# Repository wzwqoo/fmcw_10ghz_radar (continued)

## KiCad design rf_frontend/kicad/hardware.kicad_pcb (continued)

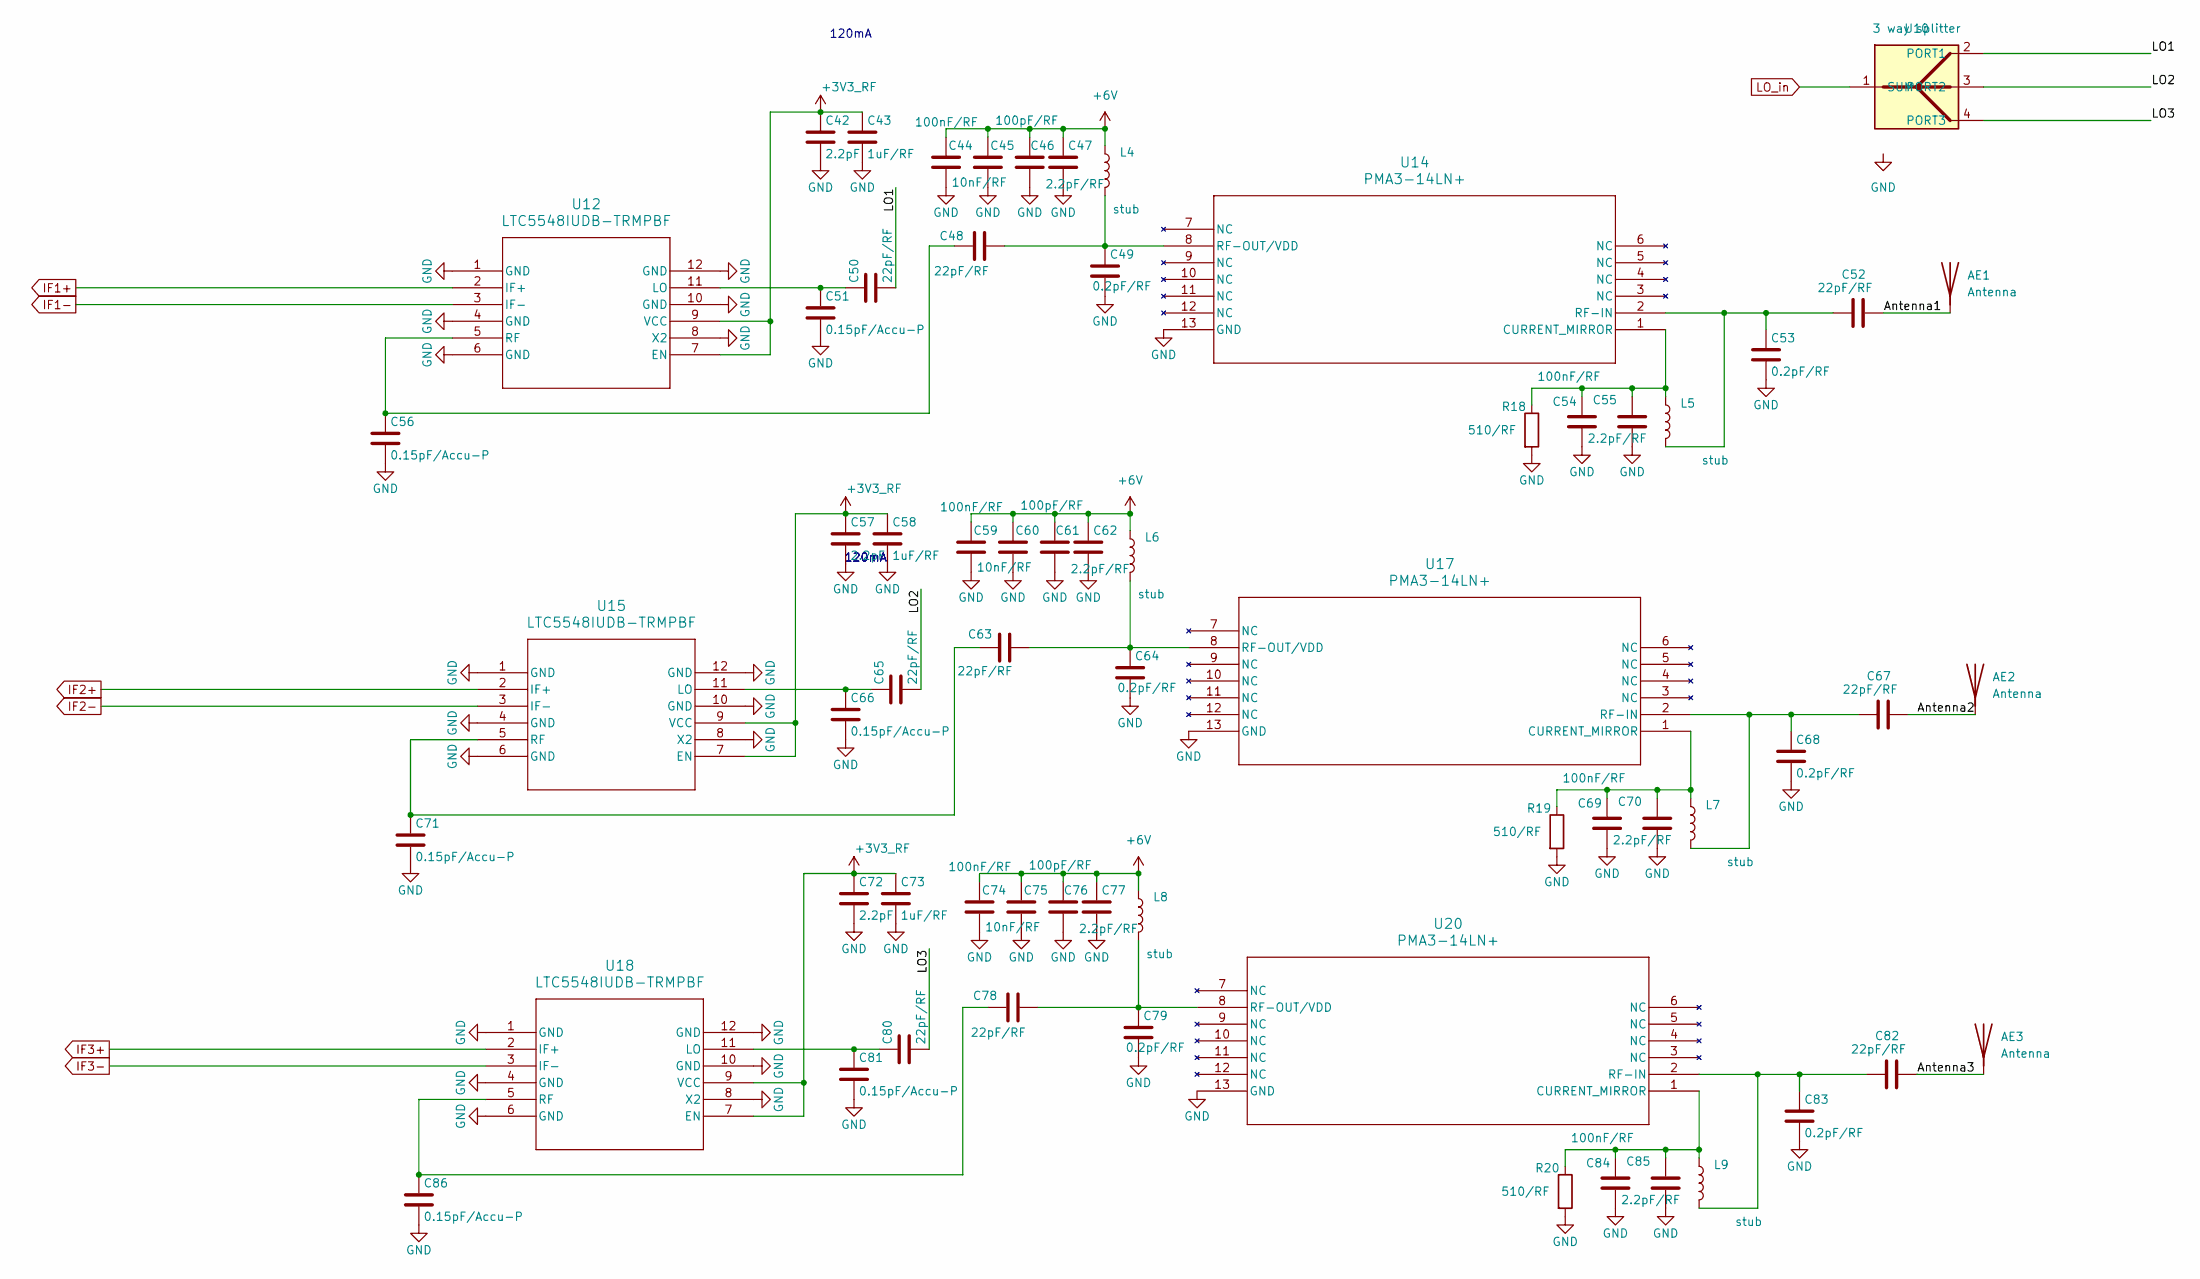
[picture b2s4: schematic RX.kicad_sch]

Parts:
AE1, AE2, AE3: Antenna; antenna
C42, C57, C72: 2.2pF; C_0201_0603Metric
C43, C58, C73: 1uF/RF; C_0402_1005Metric
C44, C54, C59, C69, C74, C84: 100nF/RF; C_0402_1005Metric
C45, C60, C75: 10nF/RF; C_0402_1005Metric
C46, C61, C76: 100pF/RF; C_0402_1005Metric
C47, C55, C62, C70, C77, C85: 2.2pF/RF; C_0402_1005Metric
C48, C50, C52, C63, C65, C67, C78, C80, C82: 22pF/RF; C_0201_0603Metric
C49, C53, C64, C68, C79, C83: 0.2pF/RF; C_0201_0603Metric
C51, C56, C66, C71, C81, C86: 0.15pF/Accu-P; C_0201_0603Metric
L4, L5, L6, L7, L8, L9: stub; NetTie-2_SMD_Pad0.5mm
R18, R19, R20: 510/RF; R_0402_1005Metric
U10: 3 way splitter; splitter
U12, U15, U18: LTC5548IUDB-TRMPBF; QFN-12-1EP_3x3mm_P0.5mm_EP1.45x1.45mm
U14, U17, U20: PMA3-14LN+; VQFN-12-1EP_4x4mm_P0.8mm_EP2.1x2.1mm; Part# PMA3-14LN+

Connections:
+3V3_RF: C42.1, C43.1, C57.1, C58.1, C72.1, C73.1, U12.7 (EN), U12.9 (VCC), U15.7 (EN), U15.9 (VCC), U18.7 (EN), U18.9 (VCC); also elsewhere on the board
+6V: C44.1, C45.1, C46.1, C47.1, C59.1, C60.1, C61.1, C62.1, C74.1, C75.1, C76.1, C77.1, L4.1, L6.1, L8.1; also elsewhere on the board
/RX/Antenna1: AE1.1 (A_1), C52.2
/RX/Antenna2: AE2.1 (A_1), C67.2
/RX/Antenna3: AE3.1 (A_1), C82.2
/RX/LO1: C50.2, U10.2 (PORT1)
/RX/LO2: C65.2, U10.3 (PORT2)
/RX/LO3: C80.2, U10.4 (PORT3)
GND: C42.2, C43.2, C44.2, C45.2, C46.2, C47.2, C49.2, C51.2, C53.2, C54.2, C55.2, C56.2, C57.2, C58.2, C59.2, C60.2, C61.2, C62.2, C64.2, C66.2, C68.2, C69.2, C70.2, C71.2, C72.2, C73.2, C74.2, C75.2, C76.2, C77.2, C79.2, C81.2, C83.2, C84.2, C85.2, C86.2, R18.2, R19.2, R20.2, U12.1 (GND), U12.4 (GND), U12.6 (GND), U12.8 (X2), U12.10 (GND), U12.12 (GND), U12.13, U14.13 (GND), U15.1 (GND), U15.4 (GND), U15.6 (GND), U15.8 (X2), U15.10 (GND), U15.12 (GND), U15.13, U17.13 (GND), U18.1 (GND), U18.4 (GND), U18.6 (GND), U18.8 (X2), U18.10 (GND), U18.12 (GND), U18.13, U20.13 (GND); also elsewhere on the board
IF1+: U12.2 (IF+); also elsewhere on the board
IF1-: U12.3 (IF-); also elsewhere on the board
IF2+: U15.2 (IF+); also elsewhere on the board
IF2-: U15.3 (IF-); also elsewhere on the board
IF3+: U18.2 (IF+); also elsewhere on the board
IF3-: U18.3 (IF-); also elsewhere on the board
LO_in: U10.1 (SUM); also elsewhere on the board
unnamed: C50.1, C51.1, U12.11 (LO)
unnamed: C48.1, C56.1, U12.5 (RF)
unnamed: C54.1, C55.1, L5.1, R18.1, U14.1 (CURRENT_MIRROR)
unnamed: C52.1, C53.1, L5.2, U14.2 (RF-IN)
unnamed: C48.2, C49.1, L4.2, U14.8 (RF-OUT/VDD)
unnamed: C65.1, C66.1, U15.11 (LO)
unnamed: C63.1, C71.1, U15.5 (RF)
unnamed: C69.1, C70.1, L7.1, R19.1, U17.1 (CURRENT_MIRROR)
unnamed: C67.1, C68.1, L7.2, U17.2 (RF-IN)
unnamed: C63.2, C64.1, L6.2, U17.8 (RF-OUT/VDD)
unnamed: C80.1, C81.1, U18.11 (LO)
unnamed: C78.1, C86.1, U18.5 (RF)
unnamed: C84.1, C85.1, L9.1, R20.1, U20.1 (CURRENT_MIRROR)
unnamed: C82.1, C83.1, L9.2, U20.2 (RF-IN)
unnamed: C78.2, C79.1, L8.2, U20.8 (RF-OUT/VDD)

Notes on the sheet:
120mA

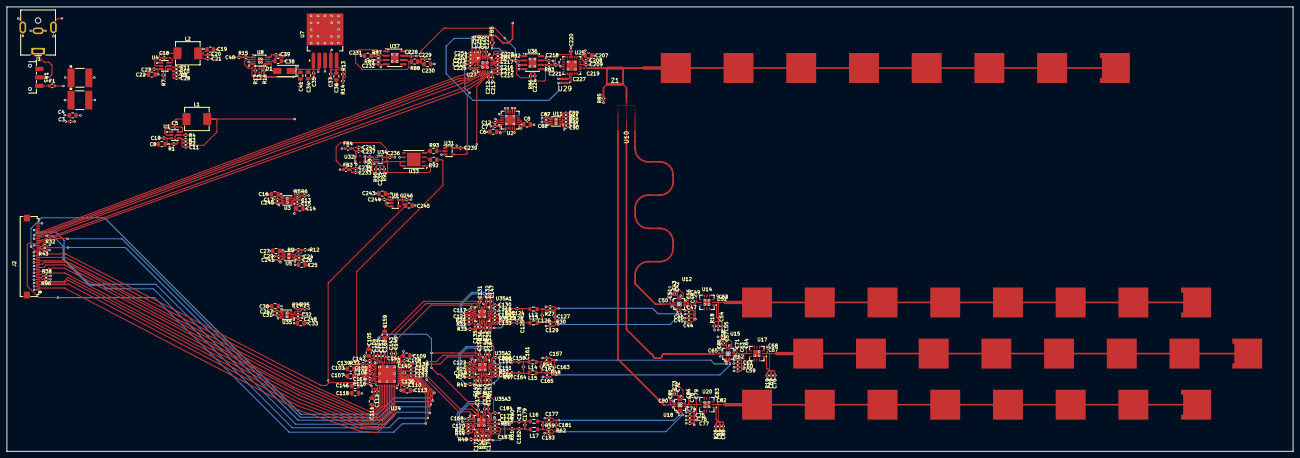
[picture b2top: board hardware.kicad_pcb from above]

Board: 4 copper layers, 377.3 x 130.4 mm, 351 parts (0 on the bottom side), 188 nets.

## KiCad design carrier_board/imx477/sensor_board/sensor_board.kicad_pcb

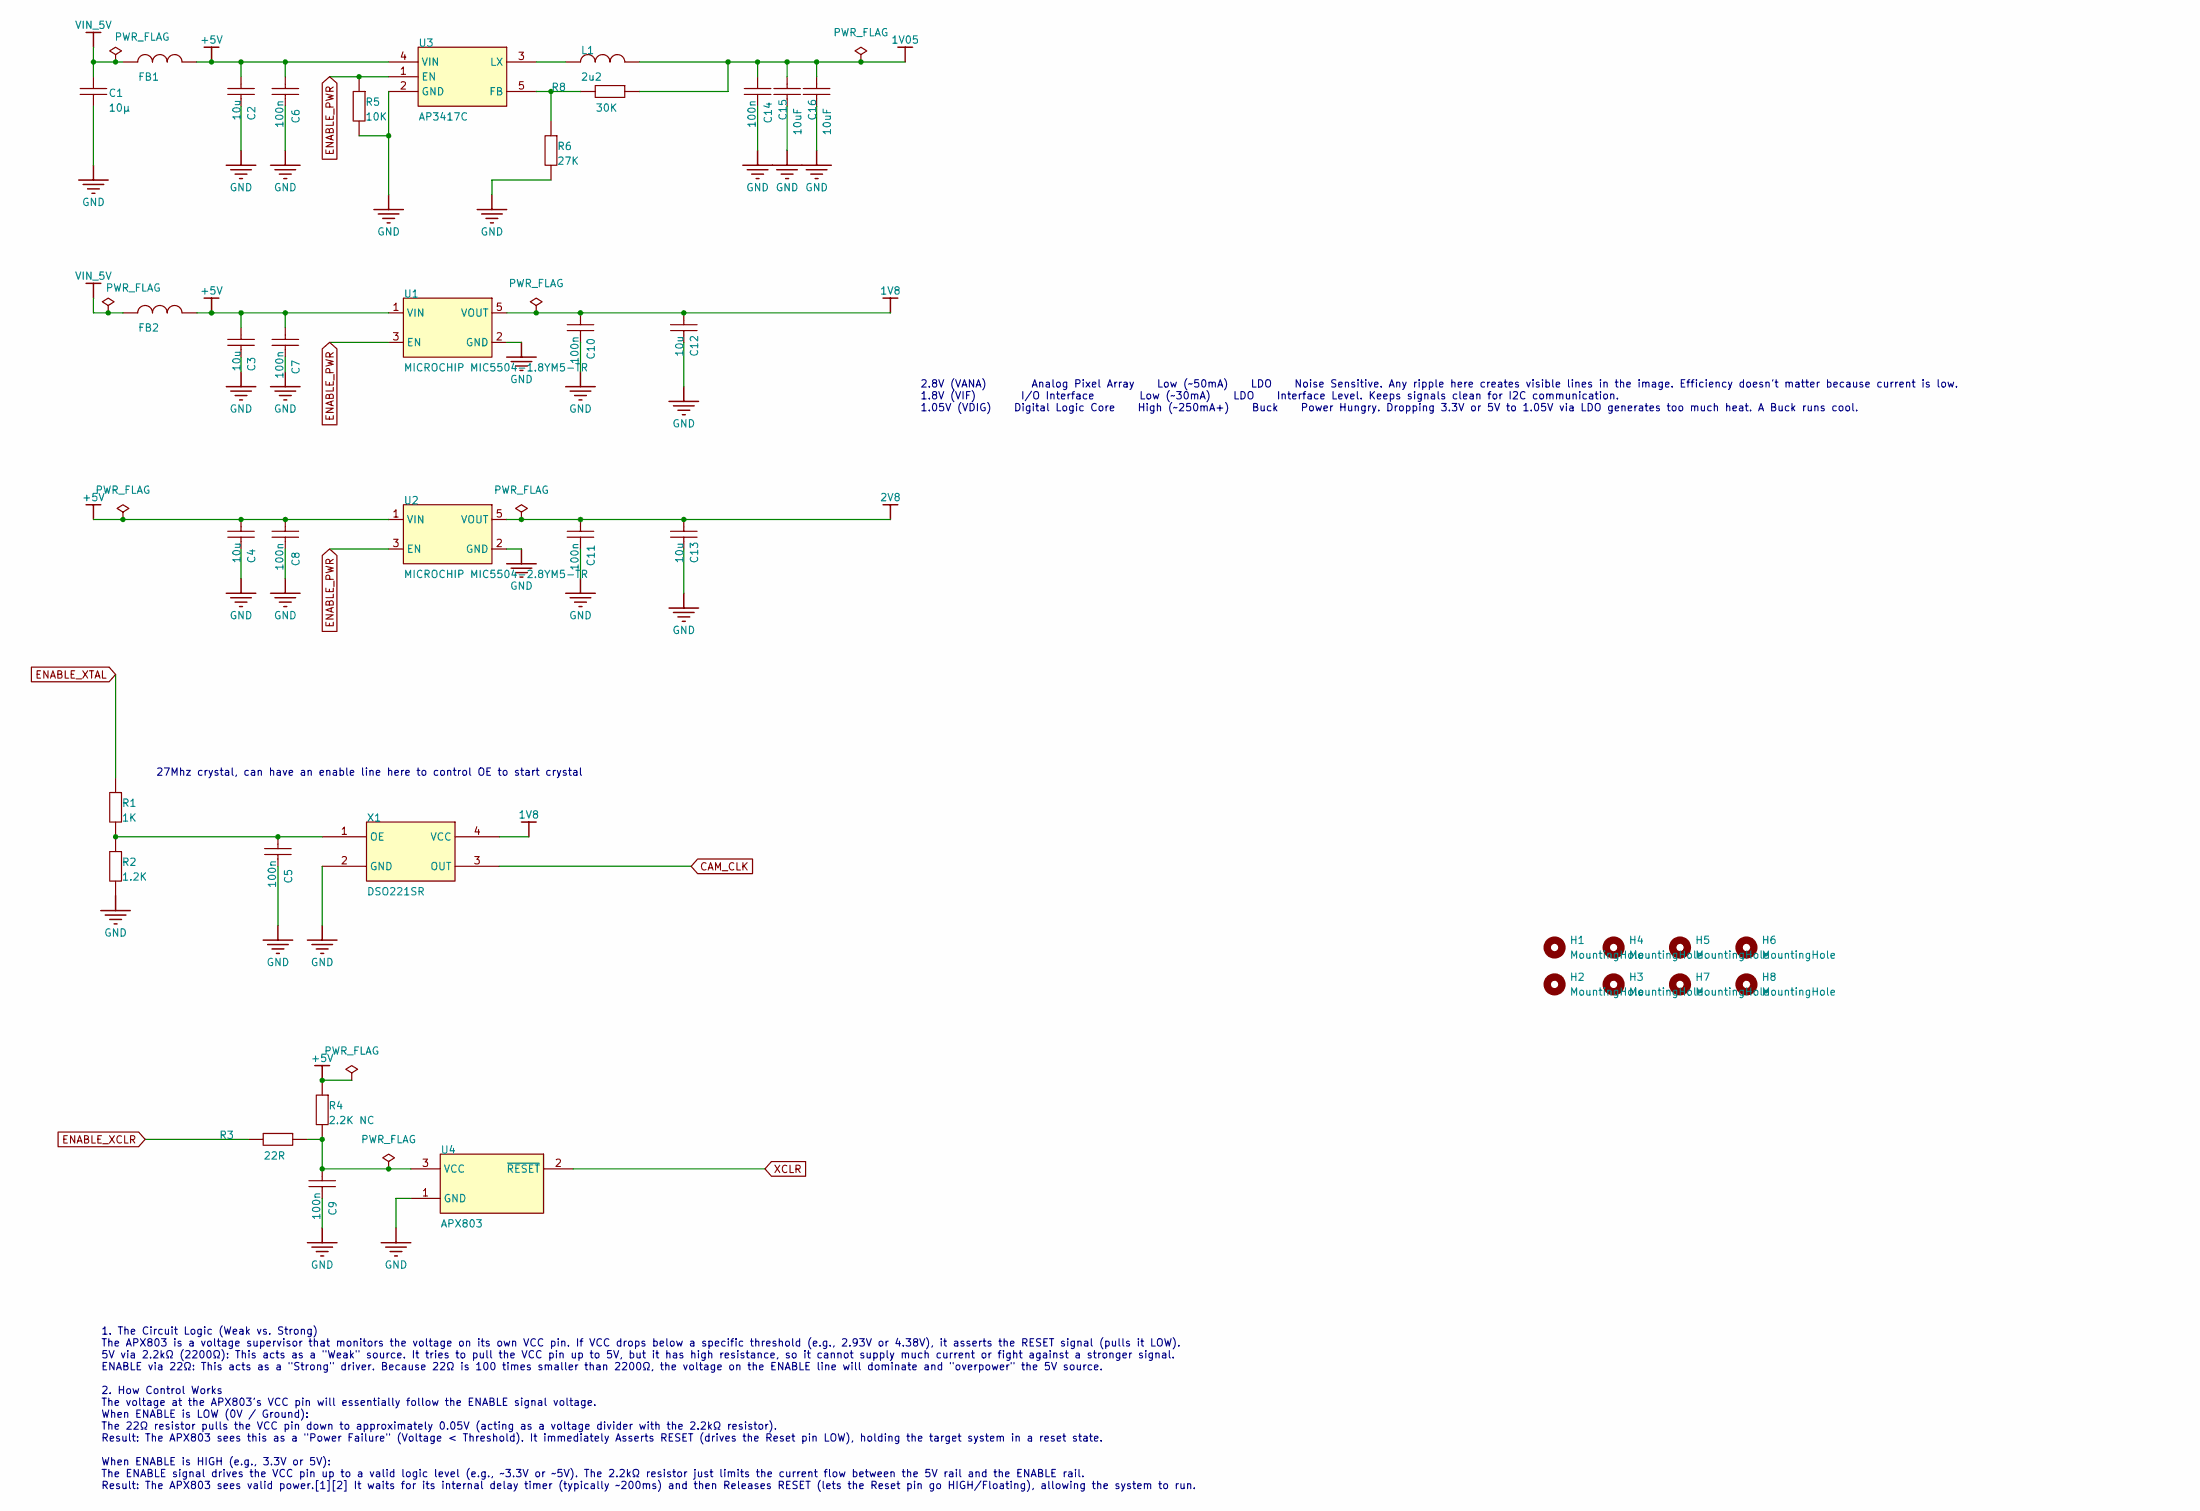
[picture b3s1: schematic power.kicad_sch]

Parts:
C1: 10uF; C_0805_2012Metric; TOLERANCE ±20%; RATINGS 50V; X5R; MANUFACTURER PART NUMBE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 UMK325BJ106MM-T; LCSC Part # C88484
C2, C3, C4, C12, C13: 10uF; C_0805_2012Metric; RATINGS 50V; NP0; VOLTAGE - RATED 50V; MANUFACTURER PART NUMBE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 06035A561JAT2A; LCSC Part # C88484
C5, C6, C7, C8, C9, C10, C11, C14: 100nF; C_0805_2012Metric; TOLERANCE ±10%; RATINGS 16V; X7R; MANUFACTURER PART NUMBE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 CC0402KRX7R7BB103; LCSC Part # C49678
C15, C16: 10uF; C_0805_2012Metric; TOLERANCE ±10%; RATINGS 16V; X5R; MANUFACTURER PART NUMBE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 EMK212BJ475KG-T; LCSC Part # C88484
FB1, FB2: 1 kΩ @ 100 MHz; L_0805_2012Metric; Part# MPZ2012S102AT000; LCSC Part # C76817
H1, H2, H3, H4, H5, H6, H7, H8: MountingHole; MountingHole_2.5mm
L1: 2u2; L_Taiyo-Yuden_MD-4040; Part# CMLO0420H2R2MTT; LCSC Part # C438930
R1: 1K; R_0805_2012Metric; RATINGS 1/16 W; TOLERANCE ±5%; MANUFACTURER PART NUMBE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 RC0402JR-073K3L; LCSC Part # C95781
R2: 1.2K; R_0805_2012Metric; RATINGS 1/16 W; TOLERANCE ±5%; MANUFACTURER PART NUMBE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 RC0402JR-073K3L; LCSC Part # C114526
R3: 22; R_0805_2012Metric; RATINGS 1/16 W; TOLERANCE ±5%; MANUFACTURER PART NUMBE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 RC0402JR-073K3L; LCSC Part # C107702
R4: 2.2K; R_0805_2012Metric; RATINGS 1/16 W; TOLERANCE ±5%; MANUFACTURER PART NUMBE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 RC0402JR-073K3L; LCSC Part # C114237
R5: 10K; R_0805_2012Metric; RATINGS 1/16 W; TOLERANCE ±5%; MANUFACTURER PART NUMBE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 RC0402JR-073K3L; LCSC Part # C100047
R6: 27K; R_0805_2012Metric; RATINGS 1/16 W; TOLERANCE ±5%; MANUFACTURER PART NUMBE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 RC0402JR-073K3L; LCSC Part # C728647
R8: 30K; R_0805_2012Metric; RATINGS 1/16 W; TOLERANCE ±5%; MANUFACTURER PART NUMBE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 RC0402JR-073K3L; LCSC Part # C126352
U1: MICROCHIP MIC5504-1.8YM5-TR; SOT-23-5; Part# MIC5504-1.8YM5-TR; LCSC Part # C626116
U2: MICROCHIP MIC5504-2.8YM5-TR; SOT-23-5; Part# MIC5504-2.8YM5-TR; LCSC Part # C95749
U3: AP3417C; SOT-23-5; Part# AP3417CKTR-G1; LCSC Part # C500759
U4: APX803; SOT-23-3; Part# APX803S-23SA-7; LCSC Part # C2067713
X1: DSO221SR; Crystal_SMD_2520-4Pin_2.5x2.0mm

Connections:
1V05: C14.2, C15.1, C16.1, L1.2, R8.2; also elsewhere on the board
1V8: C10.2, C12.1, U1.5 (VOUT), X1.4 (VCC); also elsewhere on the board
2V8: C11.2, C13.1, U2.5 (VOUT); also elsewhere on the board
+5V: C2.1, C3.1, C4.1, C6.2, C7.2, C8.2, FB1.2, FB2.2, R4.2, U1.1 (VIN), U2.1 (VIN), U3.4 (VIN)
CAM_CLK: X1.3 (OUT); also elsewhere on the board
ENABLE_PWR: R5.2, U1.3 (EN), U2.3 (EN), U3.1 (EN); also elsewhere on the board
ENABLE_XCLR: R3.1; also elsewhere on the board
ENABLE_XTAL: R1.2; also elsewhere on the board
GND: C1.2, C2.2, C3.2, C4.2, C5.1, C6.1, C7.1, C8.1, C9.1, C10.1, C11.1, C12.2, C13.2, C14.1, C15.2, C16.2, R2.1, R5.1, R6.1, U1.2 (GND), U2.2 (GND), U3.2 (GND), U4.1 (GND), X1.2 (GND); also elsewhere on the board
unnamed: R6.2, R8.1, U3.5 (FB)
unnamed: L1.1, U3.3 (LX)
unnamed: C9.2, R3.2, R4.1, U4.3 (VCC)
unnamed: C5.2, R1.1, R2.2, X1.1 (OE)
VIN_5V: C1.1, FB1.1, FB2.1; also elsewhere on the board
XCLR: U4.2 (~RESET); also elsewhere on the board

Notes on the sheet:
1. The Circuit Logic (Weak vs. Strong) The APX803 is a voltage supervisor that monitors the voltage on its own VCC pin. If VCC drops below a specific threshold (e.g., 2.93V or 4.38V), it asserts the RESET signal (pulls it LOW). 5V via 2.2kΩ (2200Ω): This acts as a "Weak" source. It tries to pull th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
2.8V (VANA) Analog Pixel Array Low (~50mA) LDO Noise Sensitive. Any ripple here creates visible lines in the image. Efficiency doesn't matter because current is low. 1.8V (VIF) I/O Interface Low (~30mA) LDO Interface Level. Keeps signals clean for I2C communication. 1.05V (VDIG) Digital Logic Core 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
27Mhz crystal, can have an enable line here to control OE to start crystal

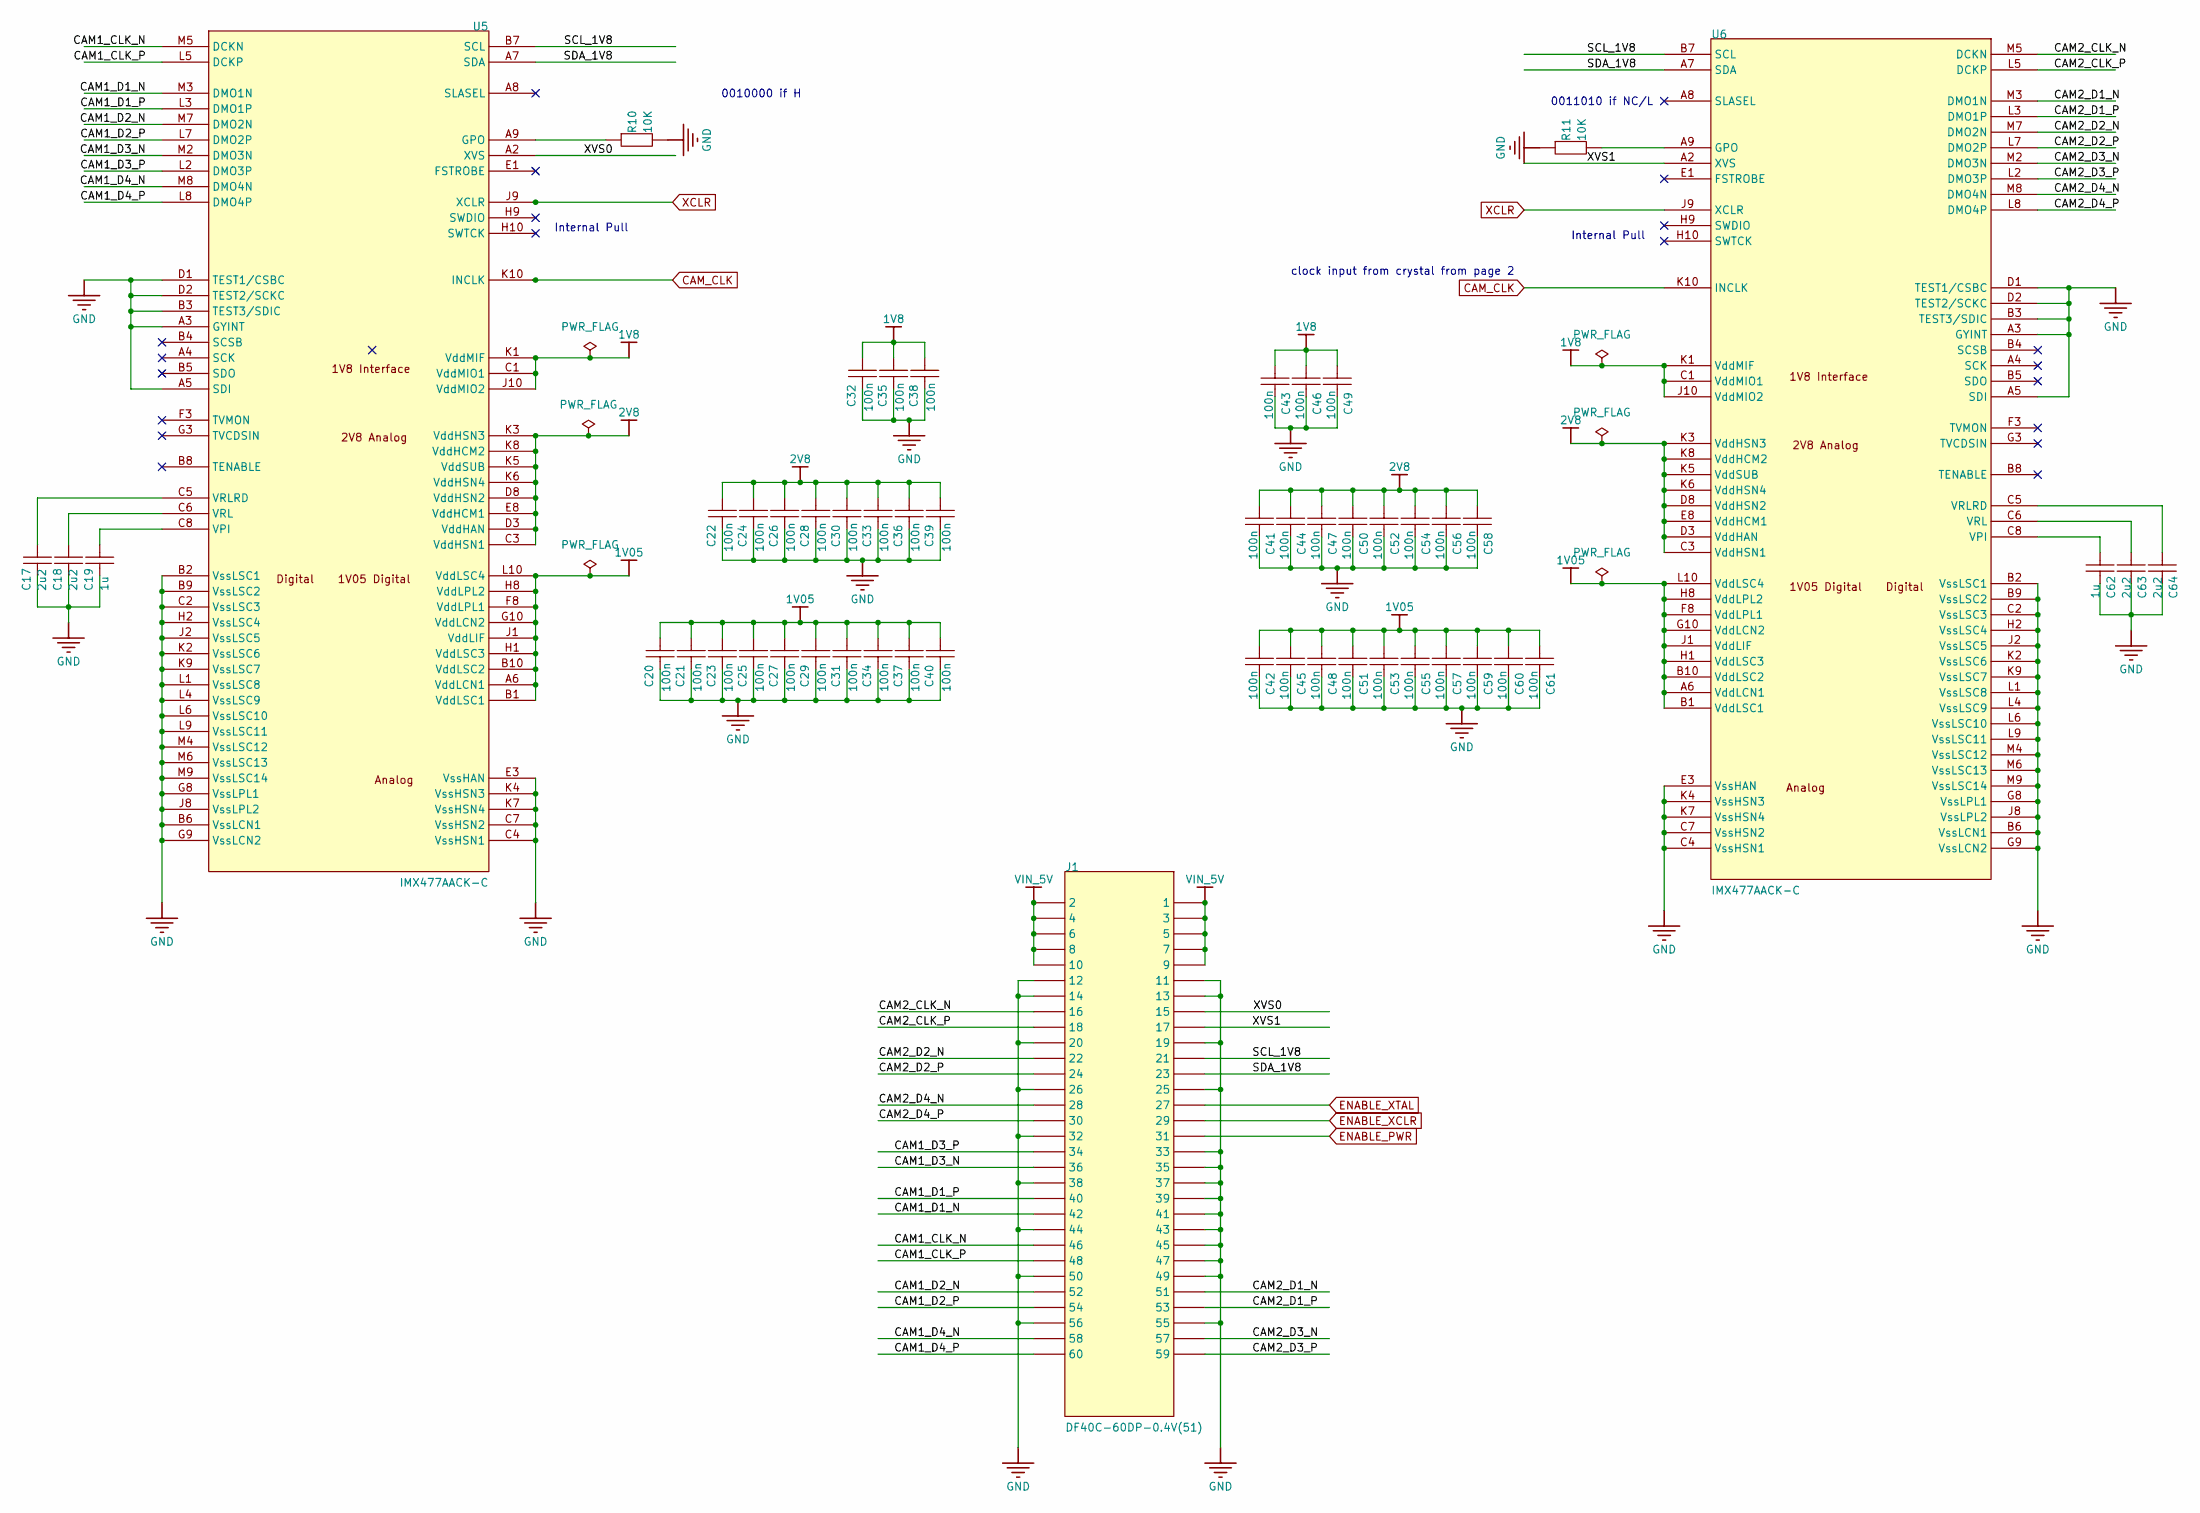
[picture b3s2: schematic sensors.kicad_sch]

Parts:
C17, C18, C19, C62, C63, C64: 10uF; C_0805_2012Metric; RATINGS 50V; NP0; VOLTAGE - RATED 50V; MANUFACTURER PART NUMBE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 06035A561JAT2A; LCSC Part # C88484
C20, C21, C22, C23, C24, C25, C26, C27, C28, C29, C30, C31, C32, C33, C34, C35, C36, C37, C38, C39, C40, C41, C42, C43, C44, C45, C46, C47, C48, C49, C50, C51, C52, C53, C54, C55, C56, C57, C58, C59, C60, C61: 100nF; C_0805_2012Metric; TOLERANCE ±10%; RATINGS 16V; X7R; MANUFACTURER PART NUMBE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 CC0402KRX7R7BB103; LCSC Part # C49678
J1: DF40C-60DP-0.4V(51); Hirose_DF40C-60DP-0.4V_2x30-1MP_P0.4mm; Part# DF40C-60DP-0.4V(51); LCSC Part # C424647
R10, R11: 10K; R_0805_2012Metric; RATINGS 1/16 W; TOLERANCE ±5%; MANUFACTURER PART NUMBE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 RC0402JR-073K3L; LCSC Part # C100047
U5, U6: IMX477AACK-C; LGA-92_L10.5-W8.5-P0.80_IMX477-AAPK-C

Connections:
1V05: C20.2, C21.2, C23.2, C25.2, C27.2, C29.2, C31.2, C34.2, C37.2, C40.2, C42.2, C45.2, C48.2, C51.2, C53.2, C55.2, C57.2, C59.2, C60.2, C61.2, U5.A6 (VddLCN1), U5.B1 (VddLSC1), U5.B10 (VddLSC2), U5.F8 (VddLPL1), U5.G10 (VddLCN2), U5.H1 (VddLSC3), U5.H8 (VddLPL2), U5.J1 (VddLIF), U5.L10 (VddLSC4), U6.A6 (VddLCN1), U6.B1 (VddLSC1), U6.B10 (VddLSC2), U6.F8 (VddLPL1), U6.G10 (VddLCN2), U6.H1 (VddLSC3), U6.H8 (VddLPL2), U6.J1 (VddLIF), U6.L10 (VddLSC4); also elsewhere on the board
1V8: C32.2, C35.2, C38.2, C43.2, C46.2, C49.2, U5.C1 (VddMIO1), U5.J10 (VddMIO2), U5.K1 (VddMIF), U6.C1 (VddMIO1), U6.J10 (VddMIO2), U6.K1 (VddMIF); also elsewhere on the board
2V8: C22.2, C24.2, C26.2, C28.2, C30.2, C33.2, C36.2, C39.2, C41.2, C44.2, C47.2, C50.2, C52.2, C54.2, C56.2, C58.2, U5.C3 (VddHSN1), U5.D3 (VddHAN), U5.D8 (VddHSN2), U5.E8 (VddHCM1), U5.K3 (VddHSN3), U5.K5 (VddSUB), U5.K6 (VddHSN4), U5.K8 (VddHCM2), U6.C3 (VddHSN1), U6.D3 (VddHAN), U6.D8 (VddHSN2), U6.E8 (VddHCM1), U6.K3 (VddHSN3), U6.K5 (VddSUB), U6.K6 (VddHSN4), U6.K8 (VddHCM2); also elsewhere on the board
/sensors/CAM1_CLK_N: J1.46, U5.M5 (DCKN)
/sensors/CAM1_CLK_P: J1.48, U5.L5 (DCKP)
/sensors/CAM1_D1_N: J1.42, U5.M3 (DMO1N)
/sensors/CAM1_D1_P: J1.40, U5.L3 (DMO1P)
/sensors/CAM1_D2_N: J1.52, U5.M7 (DMO2N)
/sensors/CAM1_D2_P: J1.54, U5.L7 (DMO2P)
/sensors/CAM1_D3_N: J1.36, U5.M2 (DMO3N)
/sensors/CAM1_D3_P: J1.34, U5.L2 (DMO3P)
/sensors/CAM1_D4_N: J1.58, U5.M8 (DMO4N)
/sensors/CAM1_D4_P: J1.60, U5.L8 (DMO4P)
/sensors/CAM2_CLK_N: J1.16, U6.M5 (DCKN)
/sensors/CAM2_CLK_P: J1.18, U6.L5 (DCKP)
/sensors/CAM2_D1_N: J1.51, U6.M3 (DMO1N)
/sensors/CAM2_D1_P: J1.53, U6.L3 (DMO1P)
/sensors/CAM2_D2_N: J1.22, U6.M7 (DMO2N)
/sensors/CAM2_D2_P: J1.24, U6.L7 (DMO2P)
/sensors/CAM2_D3_N: J1.57, U6.M2 (DMO3N)
/sensors/CAM2_D3_P: J1.59, U6.L2 (DMO3P)
/sensors/CAM2_D4_N: J1.28, U6.M8 (DMO4N)
/sensors/CAM2_D4_P: J1.30, U6.L8 (DMO4P)
/sensors/SCL_1V8: J1.21, U5.B7 (SCL), U6.B7 (SCL)
/sensors/SDA_1V8: J1.23, U5.A7 (SDA), U6.A7 (SDA)
/sensors/XVS0: J1.15, U5.A2 (XVS)
/sensors/XVS1: J1.17, U6.A2 (XVS)
CAM_CLK: U5.K10 (INCLK), U6.K10 (INCLK); also elsewhere on the board
ENABLE_PWR: J1.31; also elsewhere on the board
ENABLE_XCLR: J1.29; also elsewhere on the board
ENABLE_XTAL: J1.27; also elsewhere on the board
GND: C17.2, C18.2, C19.2, C20.1, C21.1, C22.1, C23.1, C24.1, C25.1, C26.1, C27.1, C28.1, C29.1, C30.1, C31.1, C32.1, C33.1, C34.1, C35.1, C36.1, C37.1, C38.1, C39.1, C40.1, C41.1, C42.1, C43.1, C44.1, C45.1, C46.1, C47.1, C48.1, C49.1, C50.1, C51.1, C52.1, C53.1, C54.1, C55.1, C56.1, C57.1, C58.1, C59.1, C60.1, C61.1, C62.2, C63.2, C64.2, J1.11, J1.12, J1.13, J1.14, J1.19, J1.20, J1.25, J1.26, J1.32, J1.33, J1.35, J1.37, J1.38, J1.39, J1.41, J1.43, J1.44, J1.45, J1.47, J1.49, J1.50, J1.55, J1.56, R10.1, R11.2, U5.A3 (GYINT), U5.A5 (SDI), U5.B2 (VssLSC1), U5.B3 (TEST3/SDIC), U5.B6 (VssLCN1), U5.B9 (VssLSC2), U5.C2 (VssLSC3), U5.C4 (VssHSN1), U5.C7 (VssHSN2), U5.D1 (TEST1/CSBC), U5.D2 (TEST2/SCKC), U5.E3 (VssHAN), U5.G8 (VssLPL1), U5.G9 (VssLCN2), U5.H2 (VssLSC4), U5.J2 (VssLSC5), U5.J8 (VssLPL2), U5.K2 (VssLSC6), U5.K4 (VssHSN3), U5.K7 (VssHSN4), U5.K9 (VssLSC7), U5.L1 (VssLSC8), U5.L4 (VssLSC9), U5.L6 (VssLSC10), U5.L9 (VssLSC11), U5.M4 (VssLSC12), U5.M6 (VssLSC13), U5.M9 (VssLSC14), U6.A3 (GYINT), U6.A5 (SDI), U6.B2 (VssLSC1), U6.B3 (TEST3/SDIC), U6.B6 (VssLCN1), U6.B9 (VssLSC2), U6.C2 (VssLSC3), U6.C4 (VssHSN1), U6.C7 (VssHSN2), U6.D1 (TEST1/CSBC), U6.D2 (TEST2/SCKC), U6.E3 (VssHAN), U6.G8 (VssLPL1), U6.G9 (VssLCN2), U6.H2 (VssLSC4), U6.J2 (VssLSC5), U6.J8 (VssLPL2), U6.K2 (VssLSC6), U6.K4 (VssHSN3), U6.K7 (VssHSN4), U6.K9 (VssLSC7), U6.L1 (VssLSC8), U6.L4 (VssLSC9), U6.L6 (VssLSC10), U6.L9 (VssLSC11), U6.M4 (VssLSC12), U6.M6 (VssLSC13), U6.M9 (VssLSC14); also elsewhere on the board
unnamed: R10.2, U5.A9 (GPO)
unnamed: C19.1, U5.C8 (VPI)
unnamed: C18.1, U5.C6 (VRL)
unnamed: C17.1, U5.C5 (VRLRD)
unnamed: R11.1, U6.A9 (GPO)
unnamed: C62.1, U6.C8 (VPI)
unnamed: C63.1, U6.C6 (VRL)
unnamed: C64.1, U6.C5 (VRLRD)
VIN_5V: J1.1, J1.2, J1.3, J1.4, J1.5, J1.6, J1.7, J1.8, J1.9, J1.10; also elsewhere on the board
XCLR: U5.J9 (XCLR), U6.J9 (XCLR); also elsewhere on the board

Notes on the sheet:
clock input from crystal from page 2
Internal Pull
0011010 if NC/L
0010000 if H

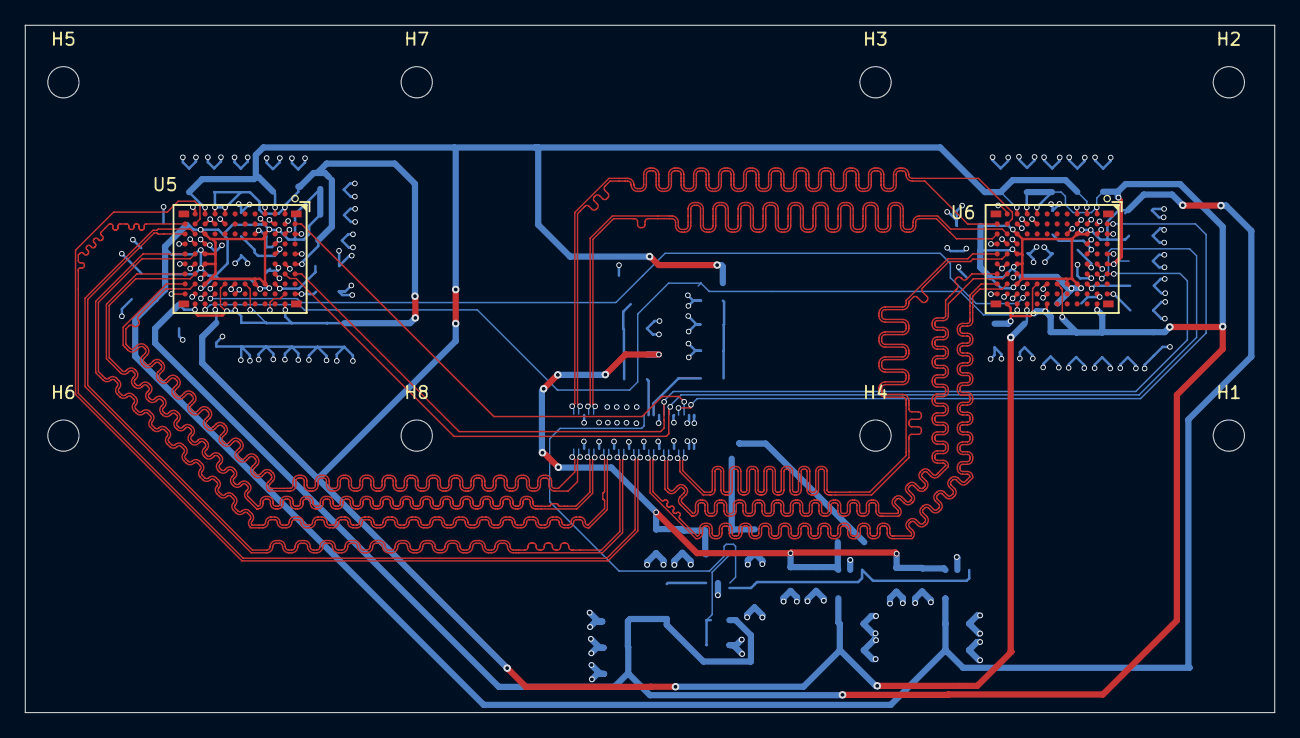
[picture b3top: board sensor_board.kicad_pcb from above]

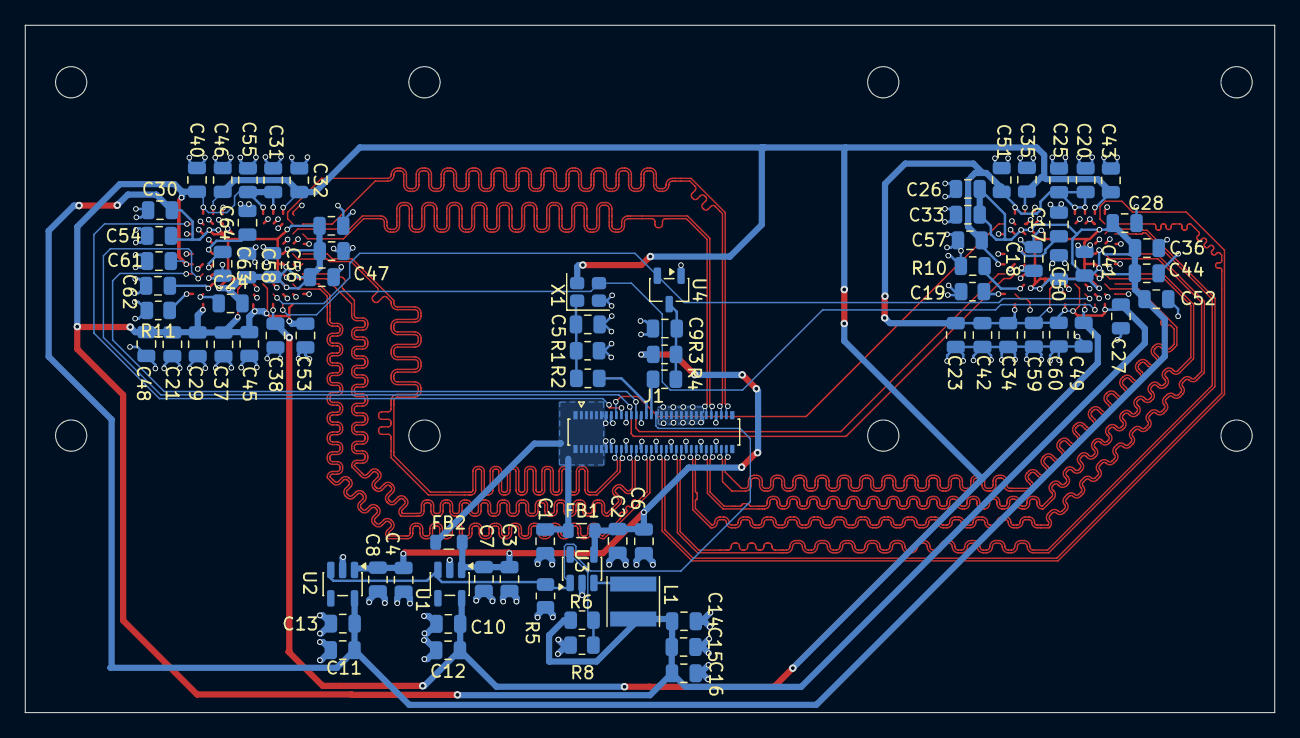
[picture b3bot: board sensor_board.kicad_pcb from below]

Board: 4 copper layers, 100.0 x 55.0 mm, 92 parts (82 on the bottom side), 47 nets.
